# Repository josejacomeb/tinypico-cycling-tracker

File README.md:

# tinypico-cycling-tracker

Tinypico based GPS + IMU + SD data logger for cycling purposes

## Components

### Software

**Programming Languages**: C++20 and Python 3.12

#### Electronic Design

- [Kicad v9.x.x](https://www.kicad.org/)
- [KiKit v1.7.x](https://yaqwsx.github.io/KiKit/latest/)

#### Integrated Development Environment

- [Arduino IDE v2.3.x](https://www.arduino.cc/en/software/)
- [Visual Studio Code](https://code.visualstudio.com/)

#### Software Libraries

- [TinyGPS++](https://github.com/mikalhart/TinyGPSPlus)
- [Electronics Cats MPU6050](https://github.com/ElectronicCats/mpu6050)
- [Embedded_UKF_Library](https://github.com/pronenewbits/Embedded_UKF_Library)
- [Pandas 2.x](https://pandas.pydata.org/)
- [gpxpy](https://github.com/tkrajina/gpxpy)
- [FilterPy v1.4.x](https://filterpy.readthedocs.io/en/latest/#)

### Hardware

- [TinyPICO](https://www.tinypico.com/): An ESP32 Dico D4 based development platform
- [uBlox-Neo6M](https://www.u-blox.com/en/product/neo-6-series): A versatile GPS Module with Antenna
- [Display OLED I2C 0.96" SSD1306](https://soldered.com/product/display-oled-i2c-white-0-96-ssd1306/): An 128x64px 0.96" OLED Display with I2C Communication
- [MPU6050](https://invensense.tdk.com/products/motion-tracking/6-axis/mpu-6050/): An integrated gyroscope and accelerometer with I2C communication
- [MicroSD Card Adapter](https://hobbycomponents.com/adapters/578-microsd-card-adapter-with-level-shifters): A SPI module to interface microcontrollers with a microSD card.

### Communication Protocols

- SPI: SD Card Reader -> TinyPICO
- I2C: OLED Screen & MPU6050 -> TinyPICO
- UART: GPS -> TinyPICO

## Instructions

### For KiCad

1. Add the symbols via the `Preferences` > `Manage symbol Libraries` > `Project Specific Libraries`, make sure that you add the `kicad-libraries` subfolders:

    1. `usini_kicad_sensors/usini_sensors.pretty`
    2. `uBlox-Neo6M/uBLox-NEO-6M.pretty`
    3. `MicroSD-Card-Adapter/MicroSD-Card-Adapter.kicad_sym`
    4. `Soldered-SSD1306-OLED-Display/Soldered.kicad_sym`
    5. `TinyPICO/TinyPICO.kicad_sym`

2. Add the footprints via the `Preferences` > `Manage Footprint Libraries` > `Project Specific Libraries`, make sure that you add the `footprint` subfolders
    1. `usini_kicad_sensors/usini_sensors.kicad_sym`
    2. `uBlox-Neo6M/uBlox-NEO-6M.kicad_sym`
    3. `MicroSD-Card-Adapter/MicroSD-Card-Adapter.kicad_sym`
    4. `Soldered-SSD1306-OLED-Display/Soldered.pretty`
    5. `TinyPICO/TinyPICO.pretty`

3. Install the `KiKit` in your local system

    ```bash
    python -m venv .venv/
    source .venv/bin/activate
    pip3 install kikit
    ```

### For Arduino

#### Run the full prototype

1. Please follow the Espressif [instructions](https://docs.espressif.com/projects/arduino-esp32/en/latest/installing.html) to support the `ESP32` boards on your Arduino.
2. Please install the following libraries in your Arduino IDE in your Tools > Manage Libraries section:
    1. [TinyPICO Helper Library](https://docs.arduino.cc/libraries/tinypico-helper-library/)
    2. [Adafruit SSD1306](https://docs.arduino.cc/libraries/adafruit-ssd1306/)
    3. [TinyGPSPlus](https://docs.arduino.cc/libraries/adafruit-ssd1306/)
3. Select the `UM TinyPICO` board in the Arduino IDE Tools > Board > ESP32
4. Select the Communication Port to `/dev/ttyACM0` if you're running on Linux.
5. Calibrate IMU as shown in the [MPU6050 Zero tutorial](https://github.com/ElectronicCats/mpu6050/wiki/4.-Examples#zero) and copy the offsets to the main code
6. Open the folder [code/arduino-tct/](code/arduino-tct/) with the IDE to flash the code to your TinyPICO Board.

#### Check other software

1. Please refer to the [code README](code/README.md) for more infomation

## Modes

The following screens were converted to `.png`  and later transformed to a compatible data with the help of the Adafruit [make_splash.py](https://github.com/adafruit/Adafruit_SSD1306/blob/master/scripts/make_splash.py) script.

### Loading

This screen show the loading in realtime of the three peripherals.

### Waiting

This is the normal screen you'll see before pushing the start button.

### Recording workout

After pushing the start button, you will see the elevation, pace, slope, altitude and workout time in the screen.

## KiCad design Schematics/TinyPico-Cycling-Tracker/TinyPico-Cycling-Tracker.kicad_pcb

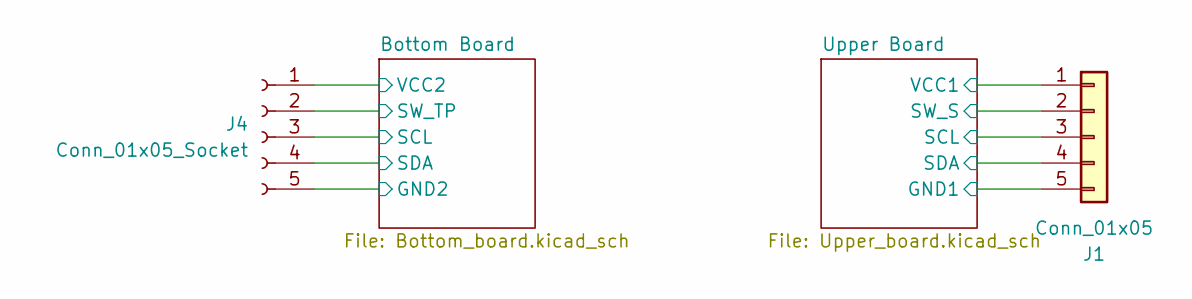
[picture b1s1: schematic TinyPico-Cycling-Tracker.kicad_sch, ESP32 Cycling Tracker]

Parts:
J1: Conn_01x05; PinHeader_1x05_P2.54mm_Vertical
J4: Conn_01x05_Socket; PinSocket_1x05_P2.54mm_Vertical

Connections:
/Bottom Board/INT: J4.5; also elsewhere on the board
/Bottom Board/SCL: J4.3; also elsewhere on the board
/Bottom Board/SDA: J4.4; also elsewhere on the board
/Bottom Board/SW_TP: J4.2; also elsewhere on the board
/Upper Board/INT: J1.5; also elsewhere on the board
/Upper Board/SCL: J1.3; also elsewhere on the board
/Upper Board/SDA: J1.4; also elsewhere on the board
/Upper Board/SW_S: J1.2; also elsewhere on the board
GND1: J1.6; also elsewhere on the board
GND2: J4.6; also elsewhere on the board
VCC1: J1.1; also elsewhere on the board
VCC2: J4.1; also elsewhere on the board

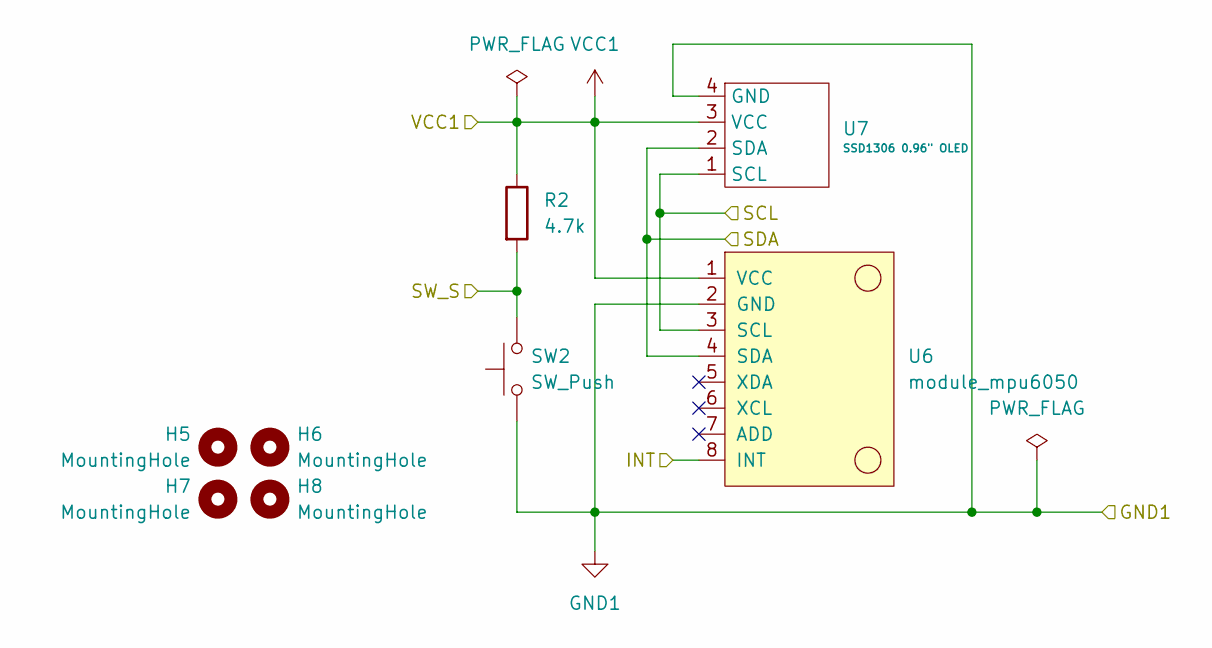
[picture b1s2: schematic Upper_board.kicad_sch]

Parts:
H5, H6, H7, H8: MountingHole; MountingHole_3mm
R2: 4.7k; R_Axial_DIN0204_L3.6mm_D1.6mm_P5.08mm_Horizontal
SW2: SW_Push; SPST_Button
U6: module_mpu6050
U7: SSD1306 0.96" OLED; Soldered-Ssd1306-OLED

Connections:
/Upper Board/INT: U6.8 (INT); also elsewhere on the board
/Upper Board/SCL: U6.3 (SCL), U7.1 (SCL); also elsewhere on the board
/Upper Board/SDA: U6.4 (SDA), U7.2 (SDA); also elsewhere on the board
/Upper Board/SW_S: R2.2, SW2.2; also elsewhere on the board
GND1: SW2.1, U6.2 (GND), U7.4 (GND); also elsewhere on the board
VCC1: R2.1, U6.1 (VCC), U7.3 (VCC); also elsewhere on the board

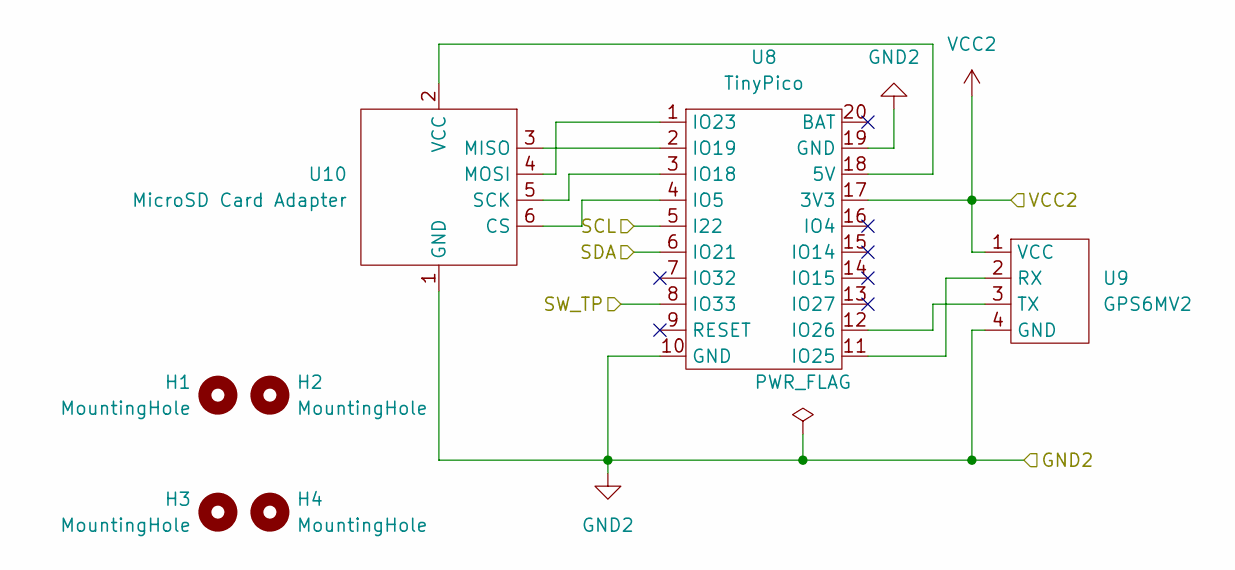
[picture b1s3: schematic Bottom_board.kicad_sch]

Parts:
H1, H2, H3, H4: MountingHole; MountingHole_3mm
U8: TinyPico; TinyPICO_V2_USBC
U9: GPS6MV2; uBlox-NEO-6M
U10: MicroSD Card Adapter; MicroSD-Card-Adapter

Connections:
/Bottom Board/INT: U8.13 (IO27); also elsewhere on the board
/Bottom Board/SCL: U8.5 (I22); also elsewhere on the board
/Bottom Board/SDA: U8.6 (IO21); also elsewhere on the board
/Bottom Board/SW_TP: U8.8 (IO33); also elsewhere on the board
GND2: U8.10 (GND), U8.19 (GND), U9.4 (GND), U10.1 (GND); also elsewhere on the board
unnamed: U8.11 (IO25), U9.2 (RX)
unnamed: U8.12 (IO26), U9.3 (TX)
unnamed: U8.4 (IO5), U10.6 (CS)
unnamed: U8.2 (IO19), U10.3 (MISO)
unnamed: U8.1 (IO23), U10.4 (MOSI)
unnamed: U8.3 (IO18), U10.5 (SCK)
unnamed: U8.18 (5V), U10.2 (VCC)
VCC2: U8.17 (3V3), U9.1 (VCC); also elsewhere on the board

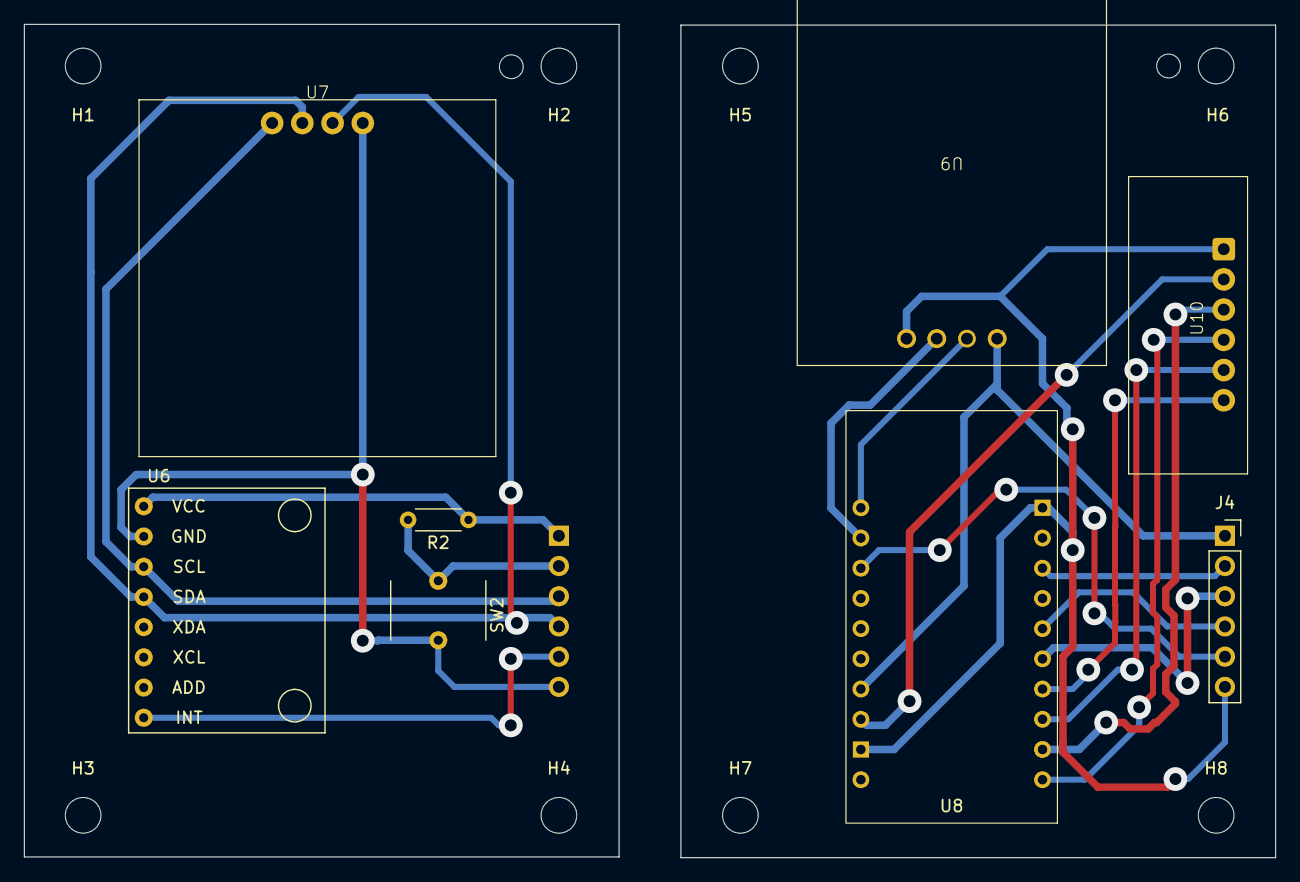
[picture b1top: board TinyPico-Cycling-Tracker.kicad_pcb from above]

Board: 2 copper layers, 105.2 x 70.1 mm, 17 parts (1 on the bottom side), 19 nets.

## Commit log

2025-11-17 chore: add IMU footprints
2025-11-18 chore: add custom uBlox-Neo6m footprint
2025-11-18 chore: add MicroSD module
2025-11-18 chore: update microsd submodule
2025-11-18 chore: update uBlox-Neo6M submodule
2025-11-19 chore: upload SSD1306 display repository
2025-11-19 chore: update the OLED folder
2025-11-19 chore: upload TinyPico files
2025-11-20 chore: update modules subfolder
2025-11-20 chore: add initial setup of the files
2025-11-20 chore: update submodules
2025-11-20 chore: load schematic with symbols
2025-11-20 chore: move libraries to a more accesible folder
2025-11-20 chore: initial schematic files
2025-11-20 fix: use 5V power pin only
2025-11-21 chore: use multisheet for the schematic
2025-11-21 chore: add double PCB design
2025-11-21 chore: add instructions for KiKit installation
2025-11-23 chore: add two pin SPST button
2025-11-23 chore: update PCB to recude the vias
2025-11-24 chore: move upper board pcb
2025-11-24 fix: down PCB to use less vias
2025-11-25 chore: add initial working program
2025-11-26 chore: split OLED code form main
2025-11-27 fix: display initialization in the .hpp file
2025-11-27 chore: splash screen & base methods - add a splash screen - Add indicators of available sensors - use base methods to manage the OLED
2025-11-28 chore: change peripherals show order and screens - Show screens with Icons - Show first the SD that loads faster
2025-11-28 chore: splash screens for the different activities - Show Icon load of the peripherals - Show waiting screen - Show activity screen
2025-11-29 chore: improve active splash screen
2025-11-30 chore: add logos in a separated .hpp file
2025-11-30 chore: add pace and distance accumulator
2025-11-30 chore: switch between altitude and elapsed time
2025-11-30 chore: Serial print only in debug mode
2025-11-30 chore: total results screen
2025-11-30 fix: avoid flickering when recording
2025-11-30 fix: move physical pin to the schematic
2025-11-30 fix: position of the MicroSD pins
2025-11-30 chore: position of Push Button & Mounting Holes
2025-11-30 chore: imrpove README
2025-11-30 chore: add the screen modes
2025-12-05 fix: summary page & states - Add a enum to manage the states - Fix the issue with the temporary summary page
2025-12-06 chore: initial cleanup of the code
2025-12-16 chore: further clean up the code
2025-12-16 chore: send data packed
2025-12-16 chore: clean up unused variables and enable LED again
2025-12-16 chore: reformat files
2025-12-16 fix: error in the time calculation
2025-12-18 chore: add UKF library
2025-12-19 chore: add initial UKF files
2025-12-19 workaroun: fix compilation file
2025-12-29 chore: UKF Implementation with acc, vel and pos
2025-12-29 chore: save UKF Predicted data on the SD
2025-12-29 fix: calculation of the longitude
2025-12-29 chore: calibrate MPU6050 & instructions fixes #17
2025-12-29 fix: calibration data types and use calibrated values
2025-12-29 chore: move constants to the appropiated file
2025-12-30 chore: data logger for validation
2025-12-31 chore: initial implementation of the UKF test
2026-01-01 chore: calculate the sensor fusion from the raw sensor data
2026-01-01 chore: improve the out files with CMake
2026-01-01 chore: remove unused parameters
2026-01-01 fix: name of the csv header row
2026-01-10 chore: adjust constants
2026-01-10 chore: improve results in the test_ukf
2026-01-18 chore: update gitignore
2026-01-18 chore: Add Python Sensor Fusion UKF
2026-01-18 chore: update utils and helper script
2026-01-18 chore: update the output names
2026-01-18 chore: remove empty values from the .csv
2026-01-18 chore: convert original sensor data for comparison
2026-01-18 chore: naive datetime and correct dt
2026-01-18 chore: pass the DT string to the script
2026-01-18 fix: naive format for the final gpx file
2026-01-18 chore: validation file between gpx files
2026-01-18 chore: validation steps for the test
2026-01-27 chore: save validation results
2026-02-27 chore: append the dirname to the output path
2026-02-27 fix: change the time column
2026-02-27 chore: improve the gitignore files
2026-03-01 chore: typo in the name
2026-03-01 fix: typo in the writter name
2026-03-02 chore: improve data logging & IMU calibration
2026-03-02 fix: generate GPX file without nan
2026-03-07 chore: add implementation details
2026-03-15 chore: save timestamp in seconds
2026-03-15 chore: resample every second, using data calculated
2026-03-15 chore: improve numerical stability of get_point_ahead
2026-03-15 chore: improve IMU implementation
2026-03-15 chore: add initial instructions
2026-03-15 chore: ignore batch scripts
2026-03-15 chore: add latest constants
2026-03-15 chore: unify constants
2026-03-15 chore: get moving distance from the gpx files
2026-03-15 chore: updated sensor fusion implementation
2026-03-15 chore: restrict decimal format
2026-03-15 chore: correct velocities and add altitude
2026-03-21 chore: vel and csv improvments
2026-03-22 chore: plot the variables in Serial Plotter
2026-03-23 fix: haversine calculation souther hemisphere
2026-03-23 chore: convert data every 1s and gps updated
2026-03-23 chore: clean up constants
2026-03-23 chore: parameters, functions improvements - Improve Q, R, P calculations - Use the haversine calculations from the utils - Recalculate process noise
2026-03-23 chore: processing on update - Use the new `gpsUpdate` variable to calculate the Update - Fix the direction of the output - Avoid to use same GPS value in case that is too near
2026-03-24 chore: standardize the lng nomenclature
2026-04-03 chore: use interrupt and calibrate
2026-04-03 chore: disable serial plotting
2026-04-04 chore: INT in schematic and PCB
2026-04-04 fix: vias warnings
2026-04-06 chore: world acceleration with course data
2026-04-18 chore: README improvements and cleanup
2026-04-19 chore: sf improvements
2026-04-19 chore: improvements in the validator
2026-04-23 chore: add sources
